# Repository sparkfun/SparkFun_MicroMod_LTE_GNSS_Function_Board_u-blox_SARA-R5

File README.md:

SparkFun MicroMod LTE GNSS Function Board - u-blox SARA-R5
========================================

[*SparkFun MicroMod LTE GNSS Function Board - u-blox SARA-R5 (DEV-18431)*](https://www.sparkfun.com/products/18431)

Using the u-blox SARA-R510M8S, this function board adds LTE and GNSS capabilities to the MicroMod EcoSystem.

Documentation
--------------
* **[Library](https://github.com/sparkfun/SparkFun_u-blox_SARA-R5_Arduino_Library)** - Arduino library for the SparkFun MicroMod LTE GNSS Function Board u-blox SARA-R5.
* **[Hookup Guide](https://docs.sparkfun.com/SparkFun_MicroMod_LTE_GNSS_Function_Board_u-blox_SARA-R5)** - Basic hookup guide for the SparkFun MicroMod LTE GNSS Function Board u-blox SARA-R5.

Product Versions
----------------
* [DEV-18431](https://www.sparkfun.com/products/18431) - Initial release, v1.1

License Information
-------------------

This product is _**open source**_!

Please review the LICENSE.md file for license information.

If you have any questions or concerns on licensing, please contact technical support on our [SparkFun forums](https://forum.sparkfun.com/viewforum.php?f=152).

Distributed as-is; no warranty is given.

- Your friends at SparkFun.

_<COLLABORATION CREDIT>_

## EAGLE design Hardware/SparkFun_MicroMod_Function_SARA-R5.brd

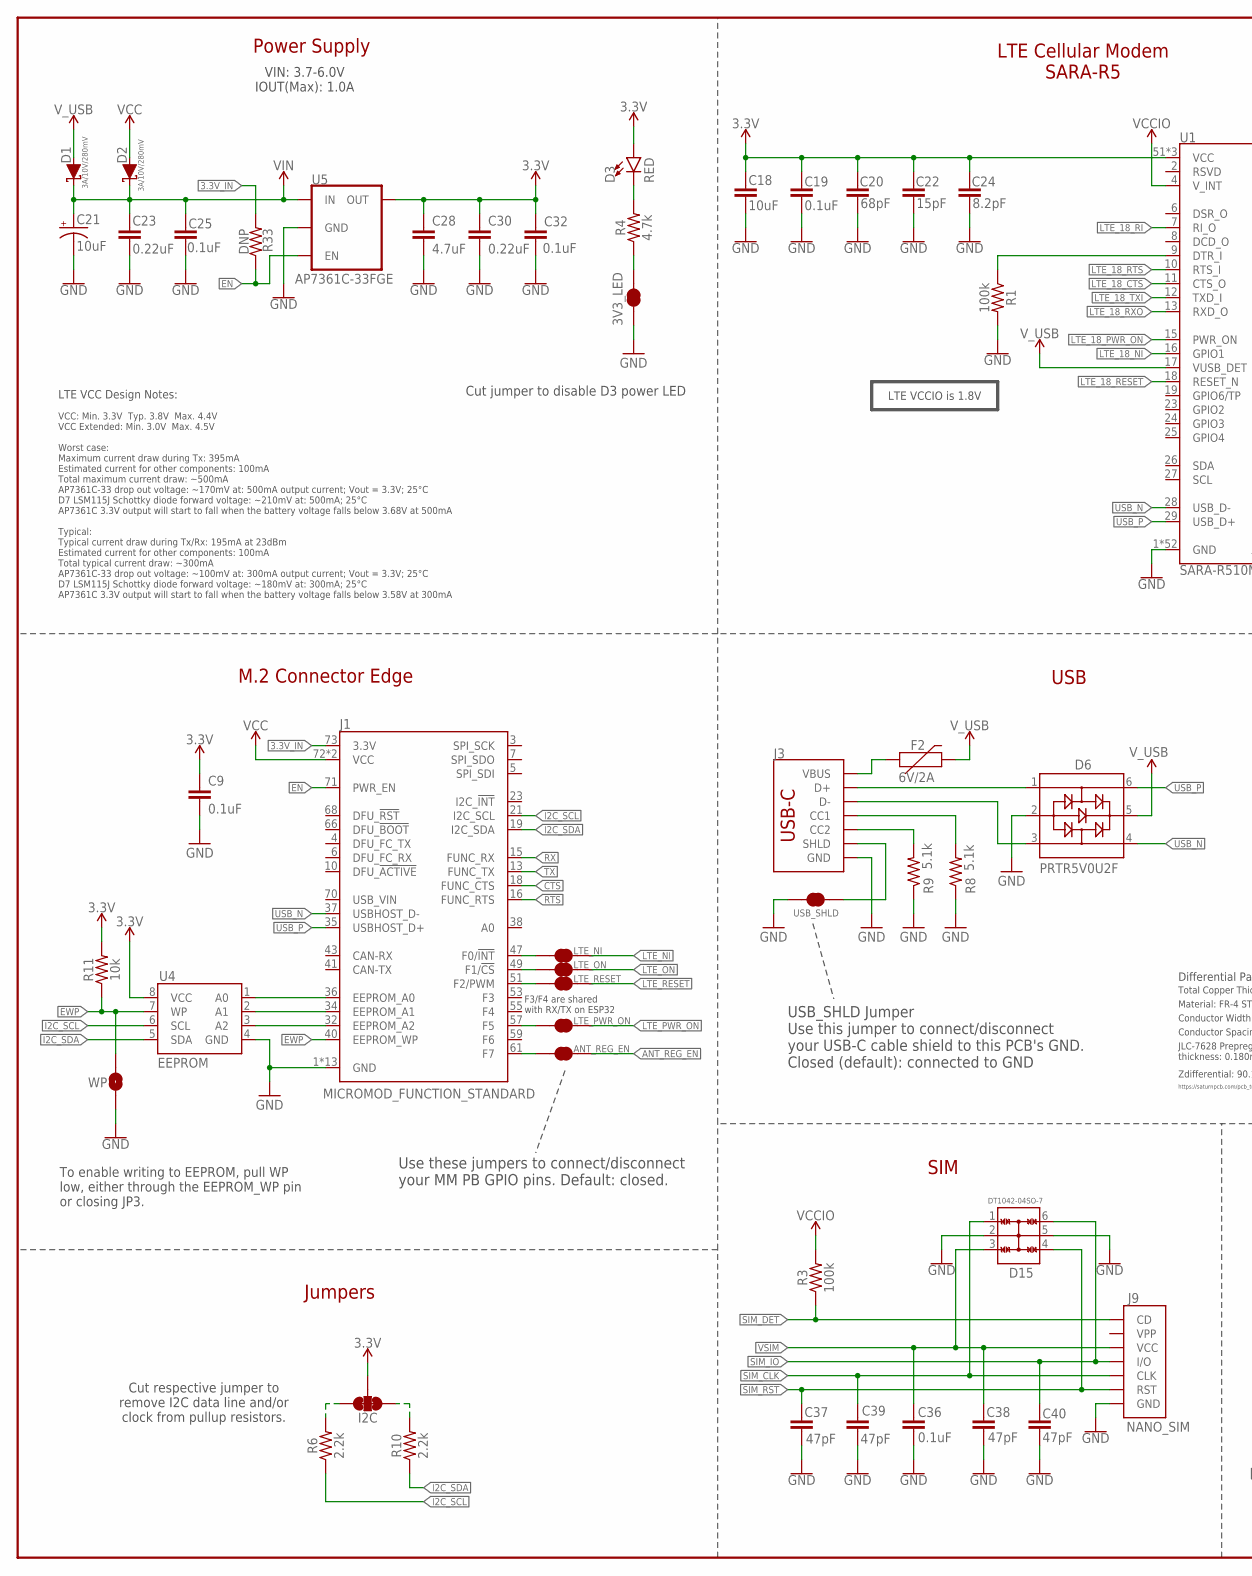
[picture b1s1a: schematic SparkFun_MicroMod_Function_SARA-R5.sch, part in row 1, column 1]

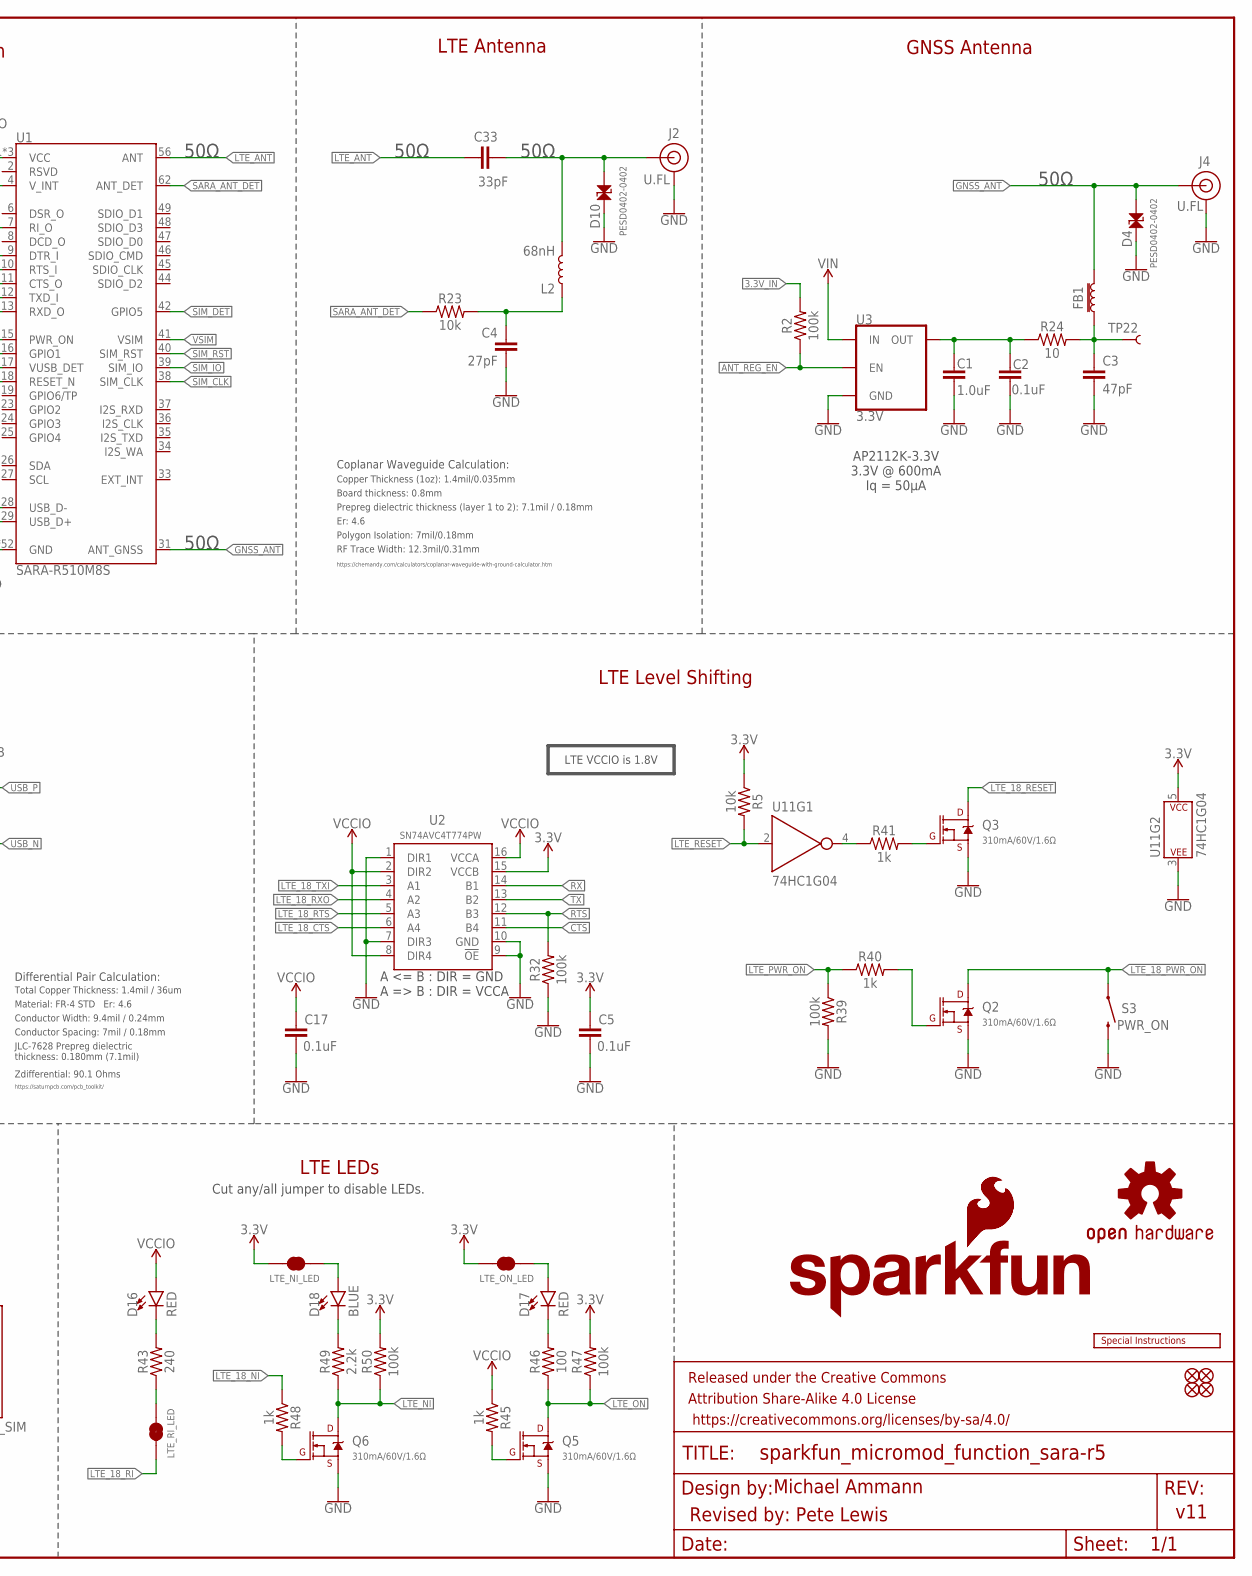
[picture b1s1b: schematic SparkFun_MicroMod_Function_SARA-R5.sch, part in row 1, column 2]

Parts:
3V3_LED: JUMPER-SMT_2_NC_TRACE_SILK; SMT-JUMPER_2_NC_TRACE_SILK
ANT_REG_EN: JUMPER-SMT_2_NC_TRACE_SILK; SMT-JUMPER_2_NC_TRACE_SILK
C1: 1.0uF; 0603
C2, C5, C9, C17, C19, C25, C32, C36: 0.1uF; 0402-TIGHT
C3, C37, C38, C39, C40: 47pF; 0603
C4: 27pF; 0402
C18: 10uF; 0603
C20: 68pF; 0603
C21: 10uF; EIA3216
C22: 15pF; 0603
C23, C30: 0.22uF; 0603
C24: 8.2pF; 0603
C28: 4.7uF; 0603
C33: 33pF; 0402-TIGHT
D1, D2: 3A/10V/280mV; SOD-323
D3, D16, D17: RED; LED-0603
D4, D10: PESD0402-0402; 0402
D6: PRTR5V0U2F; SOT886
D15: DT1042-04SO-7; SOT23-6L
D18: BLUE; LED-0603
F2: 6V/2A; 1210
FB1: 30Ω/1.8A; 0603
FD1, FD2, FD3, FD4: FIDUCIALUFIDUCIAL; FIDUCIAL-MICRO
FRAME2: FRAME-LEDGER; CREATIVE_COMMONS
I2C: JUMPER-SMT_3_2-NC_TRACE_SILK; SMT-JUMPER_3_2-NC_TRACE_SILK
J1: MICROMOD_FUNCTION_STANDARD; M.2-CARD-E-22_FUNCTION_STANDARD
J2, J4: U.FL
J3: USB_C_2-LAYER_PADS; USB-C-16P-2LAYER-PADS
J9: NANO_SIM; NANO_SIM_PP
L2: 68nH; 0402_COILCRAFT
LOGO1: SFE_LOGO_NAME_FLAME.2_INCH; SFE_LOGO_NAME_FLAME_.2
LOGO2: SFE_LOGO_FLAME.2_INCH; SFE_LOGO_FLAME_.2
LOGO3: SPECIAL_INSTRUCTIONS-ORDERING; ORDERING_INSTRUCTIONS
LOGO4: OSHW-LOGOMINI; OSHW-LOGO-MINI
LTE_NI: JUMPER-SMT_2_NC_TRACE_SILK; SMT-JUMPER_2_NC_TRACE_SILK
LTE_NI_LED: JUMPER-SMT_2_NC_TRACE_SILK; SMT-JUMPER_2_NC_TRACE_SILK
LTE_ON: JUMPER-SMT_2_NC_TRACE_SILK; SMT-JUMPER_2_NC_TRACE_SILK
LTE_ON_LED: JUMPER-SMT_2_NC_TRACE_SILK; SMT-JUMPER_2_NC_TRACE_SILK
LTE_PWR_ON: JUMPER-SMT_2_NC_TRACE_SILK; SMT-JUMPER_2_NC_TRACE_SILK
LTE_RESET: JUMPER-SMT_2_NC_TRACE_SILK; SMT-JUMPER_2_NC_TRACE_SILK
LTE_RI_LED: JUMPER-SMT_2_NC_TRACE_SILK; SMT-JUMPER_2_NC_TRACE_SILK
Q2, Q3, Q5, Q6: 310mA/60V/1.6Ω; SOT323
R1, R2, R3, R32, R39, R47, R50: 100k; 0402-TIGHT
R4: 4.7k; 0402-TIGHT
R5, R11, R23: 10k; 0402-TIGHT
R6, R10, R49: 2.2k; 0402-TIGHT
R8, R9: 5.1k; 0402-TIGHT
R24: 10; 0603
R33: DNP; 0402-TIGHT
R40, R41, R45, R48: 1k; 0402-TIGHT
R43: 240; 0603
R46: 100; 0603
S3: PWR_ON; TACTILE_SWITCH_SMD_4.6X2.8MM
TP22: TEST-POINT3X4; PAD.03X.04
U1: SARA-R510M8S; SARA-LGA
U2: SN74AVC4T774PW; SOP65P640X120-16N
U3: 3.3V; SOT23-5
U4: EEPROM; SO08
U5: AP7361C-33FGE; UDFN-8
U11: 74HC1G04; SOT353
USB_SHLD: JUMPER-SMT_2_NC_TRACE_SILK; SMT-JUMPER_2_NC_TRACE_SILK
WP: JUMPER-SMT_2_NO_SILK; SMT-JUMPER_2_NO_SILK

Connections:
3.3V: C5.1, C9.1, C18.1, C19.1, C20.1, C22.1, C24.1, C28.1, C30.1, C32.1, D3.A, I2C.2, LTE_NI_LED.2, LTE_ON_LED.2, R5.1, R11.2, R47.2, R50.2, U1.51 (VCC), U1.52 (VCC), U1.53 (VCC), U2.15 (VCCB), U4.8 (VCC), U5.1 (OUT), U11.5 (P$V+)
3.3V_IN: J1.73 (3.3V), R2.2, R33.2
ANT_REG_EN: ANT_REG_EN.1, R2.1, U3.3 (EN)
CTS: J1.18 (FUNC_CTS), U2.11 (B4)
EN: J1.71 (PWR_EN), R33.1, U5.5 (EN)
EWP: J1.40 (EEPROM_WP), R11.1, U4.7 (WP), WP.2
GND: 3V3_LED.1, C1.2, C2.2, C3.2, C4.2, C5.2, C9.2, C17.2, C18.2, C19.2, C20.2, C21.-, C22.2, C23.2, C24.2, C25.2, C28.2, C30.2, C32.2, C36.1, C37.2, C38.1, C39.2, C40.1, D4.2, D6.2, D10.2, D15.2, D15.5, J1.1 (GND), J1.2 (GND), J1.8 (GND), J1.33 (GND), J1.39 (GND), J1.45 (GND), J1.75 (GND), J1.GND1 (GND), J1.GND2 (GND), J1.GND3 (GND), J1.GND4 (GND), J1.GND5 (GND), J1.GND6 (GND), J2.1 (GND), J2.2 (GND), J3.GND, J3.GND2 (GND), J4.1 (GND), J4.2 (GND), J9.A1 (GND), J9.A2 (GND), J9.A3 (GND), J9.A4 (GND), J9.C5 (GND), Q2.2 (S), Q3.2 (S), Q5.2 (S), Q6.2 (S), R1.2, R8.1, R9.1, R32.1, R39.2, S3.3 (2), S3.4 (2), U1.1 (GND), U1.3 (GND), U1.5 (GND), U1.14 (GND), U1.20 (GND), U1.21 (GND), U1.22 (GND), U1.30 (GND), U1.32 (GND), U1.43 (GND), U1.50 (GND), U1.54 (GND), U1.55 (GND), U1.57 (GND), U1.58 (GND), U1.59 (GND), U1.60 (GND), U1.61 (GND), U1.63 (GND), U1.64 (GND), U1.65 (GND), U1.66 (GND), U1.67 (GND), U1.68 (GND), U1.69 (GND), U1.70 (GND), U1.71 (GND), U1.72 (GND), U1.73 (GND), U1.74 (GND), U1.75 (GND), U1.76 (GND), U1.77 (GND), U1.78 (GND), U1.79 (GND), U1.80 (GND), U1.81 (GND), U1.82 (GND), U1.83 (GND), U1.84 (GND), U1.85 (GND), U1.86 (GND), U1.87 (GND), U1.88 (GND), U1.89 (GND), U1.90 (GND), U1.91 (GND), U1.92 (GND), U1.93 (GND), U1.94 (GND), U1.95 (GND), U1.96 (GND), U2.1 (DIR1), U2.7 (DIR3), U2.9 (!OE), U2.10 (GND), U3.2 (GND), U4.4 (GND), U5.4 (GND), U5.EP (GND), U11.3 (P$V-), USB_SHLD.2, WP.1
GNSS_ANT: D4.1, FB1.2, J4.FEED (SIGNAL), U1.31 (ANT_GNSS)
I2C_SCL: J1.21 (I2C_SCL), R6.1, U4.6 (SCL)
I2C_SDA: J1.19 (I2C_SDA), R10.1, U4.5 (SDA)
LTE_18_!RESET!: Q3.3 (D), U1.18 (RESET_N)
LTE_18_CTS: U1.11 (CTS_O), U2.6 (A4)
LTE_18_DTR: R1.1, U1.9 (DTR_I)
LTE_18_NI: R48.1, U1.16 (GPIO1)
LTE_18_PWR_ON: Q2.3 (D), S3.1, S3.2 (1), U1.15 (PWR_ON)
LTE_18_RI: LTE_RI_LED.2, U1.7 (RI_O)
LTE_18_RTS: U1.10 (RTS_I), U2.5 (A3)
LTE_18_RXO: U1.13 (RXD_O), U2.4 (A2)
LTE_18_TXI: U1.12 (TXD_I), U2.3 (A1)
LTE_!NI!: LTE_NI.1, Q6.3 (D), R49.1, R50.1
LTE_!ON!: LTE_ON.1, Q5.3 (D), R46.1, R47.1
LTE_!RESET!: LTE_RESET.1, R5.2, U11.2 (A)
LTE_ANT: C33.1, U1.56 (ANT)
LTE_PWR_ON: LTE_PWR_ON.1, R39.1, R40.1
unnamed: J1.36 (EEPROM_A0), U4.1 (A0)
unnamed: J3.A5 (CC1), R8.2
unnamed: J1.57 (F5), LTE_PWR_ON.2
unnamed: ANT_REG_EN.2, J1.61 (F7)
unnamed: J3.B5 (CC2), R9.2
unnamed: 3V3_LED.2, R4.1
unnamed: D3.C, R4.2
unnamed: J1.32 (EEPROM_A2), U4.3 (A2)
unnamed: J1.34 (EEPROM_A1), U4.2 (A1)
unnamed: D6.1, J3.A6 (D+), J3.B6 (D+)
unnamed: C33.2, D10.1, J2.FEED (SIGNAL), L2.P$2 (2)
unnamed: J1.47 (F0/!INT!), LTE_NI.2
unnamed: I2C.1, R10.2
unnamed: I2C.3, R6.2
unnamed: D6.3, J3.A7 (D-), J3.B7 (D-)
unnamed: J1.49 (F1/!CS!), LTE_ON.2
unnamed: J1.51 (F2/PWM), LTE_RESET.2
unnamed: C4.1, L2.P$1 (1), R23.2
unnamed: D18.A, LTE_NI_LED.1
unnamed: LTE_RI_LED.1, R43.1
unnamed: D17.A, LTE_ON_LED.1
unnamed: F2.1, J3.VBUS1 (VBUS), J3.VBUS2 (VBUS)
unnamed: C1.1, C2.1, R24.1, U3.5 (OUT)
unnamed: C3.1, FB1.1, R24.2, TP22.1
unnamed: Q2.1 (G), R40.2
unnamed: Q3.1 (G), R41.2
unnamed: R41.1, U11.4 (Y)
unnamed: D16.C, R43.2
unnamed: Q6.1 (G), R48.2
unnamed: D18.C, R49.2
unnamed: Q5.1 (G), R45.2
unnamed: D17.C, R46.2
RTS: J1.16 (FUNC_RTS), R32.2, U2.12 (B3)
RX: J1.15 (FUNC_RX), U2.14 (B1)
SARA_ANT_DET: R23.1, U1.62 (ANT_DET)
SHLD: J3.SHLD1 (SHLD), J3.SHLD2 (SHLD), J3.SHLD3 (SHLD), J3.SHLD4 (SHLD), USB_SHLD.1
SIM_CLK: C39.1, D15.1, J9.C3 (CLK), U1.38 (SIM_CLK)
SIM_DET: J9.CD, R3.1, U1.42 (GPIO5)
SIM_IO: C40.2, D15.6, J9.C7 (I/O), U1.39 (SIM_IO)
SIM_RST: C37.1, D15.4, J9.C2 (RST), U1.40 (SIM_RST)
TX: J1.13 (FUNC_TX), U2.13 (B2)
USB_N: D6.4, J1.37 (USBHOST_D-), U1.28 (USB_D-)
USB_P: D6.6, J1.35 (USBHOST_D+), U1.29 (USB_D+)
VCC: D2.A, J1.72 (VCC), J1.74 (VCC)
VCCIO: C17.1, D16.A, R3.2, R45.1, U1.4 (V_INT), U2.2 (DIR2), U2.8 (DIR4), U2.16 (VCCA)
VIN: C21.+, C23.1, C25.1, D1.C, D2.C, U3.1 (IN), U5.8 (IN)
VSIM: C36.2, C38.2, D15.3, J9.C1 (VCC), U1.41 (VSIM)
V_USB: D1.A, D6.5, F2.2, U1.17 (VUSB_DET)

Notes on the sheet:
Michael Ammann
v11
M.2 Connector Edge
Power Supply
Jumpers
Cut respective jumper to remove I2C data line and/or clock from pullup resistors.
To enable writing to EEPROM, pull WP low, either through the EEPROM_WP pin or closing JP3.
Cut jumper to disable D3 power LED
LTE VCC Design Notes:
VCC: Min. 3.3V Typ. 3.8V Max. 4.4V VCC Extended: Min. 3.0V Max. 4.5V Worst case: Maximum current draw during Tx: 395mA Estimated current for other components: 100mA Total maximum current draw: ~500mA AP7361C-33 drop out voltage: ~170mV at: 500mA output current; Vout = 3.3V; 25°C D7 LSM115J Schottky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
VIN: 3.7-6.0V IOUT(Max): 1.0A
LTE Cellular Modem SARA-R5
SIM
50Ω
LTE VCCIO is 1.8V
LTE Antenna
LTE LEDs
LTE Level Shifting
USB
F3/F4 are shared with RX/TX on ESP32
Revised by: Pete Lewis
GNSS Antenna
AP2112K-3.3V 3.3V @ 600mA Iq = 50µA
Material: FR-4 STD Er: 4.6
Total Copper Thickness: 1.4mil / 36um
Conductor Spacing: 7mil / 0.18mm
Conductor Width: 9.4mil / 0.24mm
JLC-7628 Prepreg dielectric thickness: 0.180mm (7.1mil)
https://saturnpcb.com/pcb_toolkit/
Differential Pair Calculation:
Zdifferential: 90.1 Ohms
USB_SHLD Jumper Use this jumper to connect/disconnect your USB-C cable shield to this PCB's GND. Closed (default): connected to GND
Board thickness: 0.8mm
Er: 4.6
Copper Thickness (1oz): 1.4mil/0.035mm
RF Trace Width: 12.3mil/0.31mm
Polygon Isolation: 7mil/0.18mm
Prepreg dielectric thickness (layer 1 to 2): 7.1mil / 0.18mm
https://chemandy.com/calculators/coplanar-waveguide-with-ground-calculator.htm
Coplanar Waveguide Calculation:

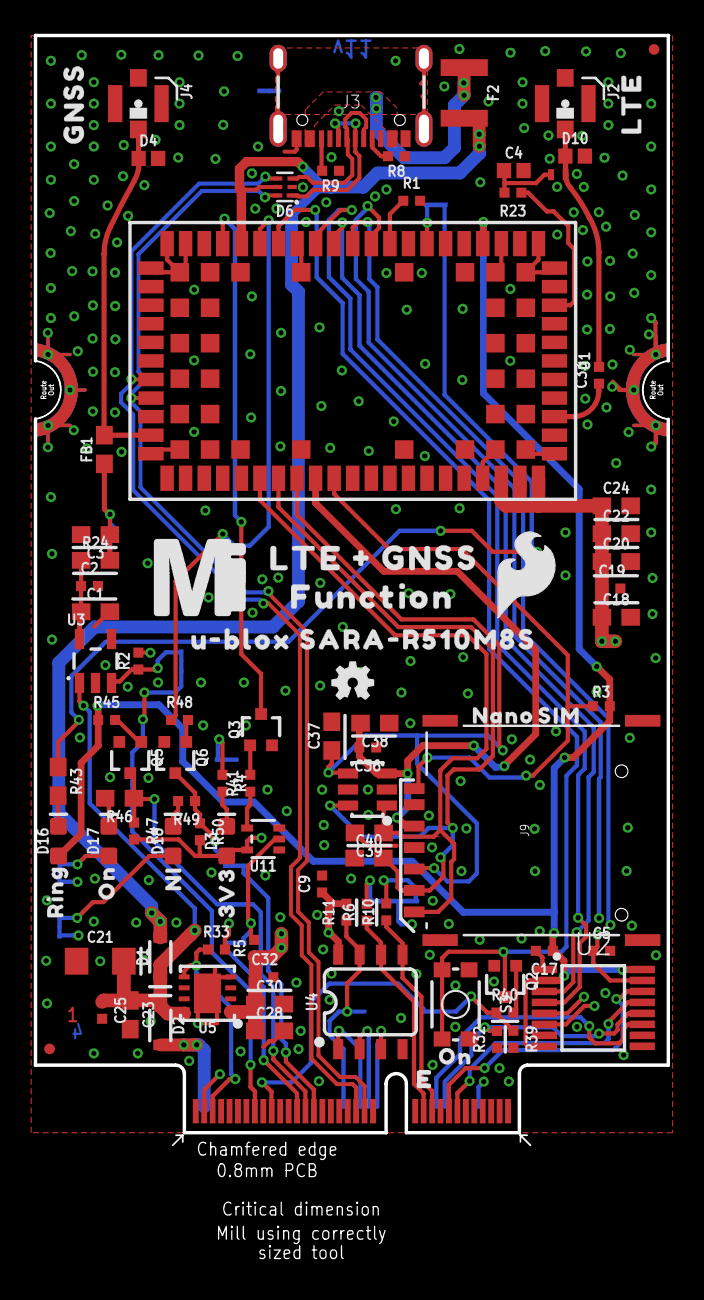
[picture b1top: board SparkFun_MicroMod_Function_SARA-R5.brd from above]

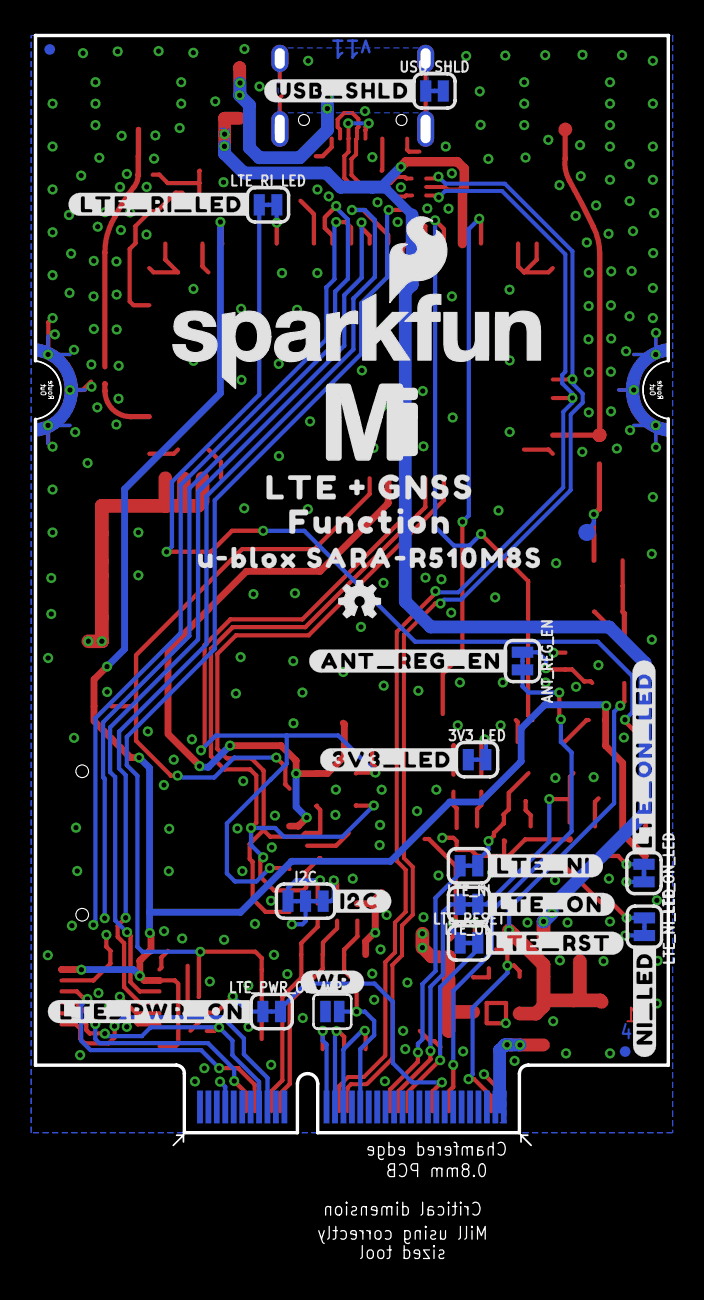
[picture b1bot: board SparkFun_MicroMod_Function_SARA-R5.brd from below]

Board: 4 copper layers, 37.5 x 65.8 mm, 129 parts (33 on the bottom side), 72 nets.

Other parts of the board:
LOGO6: OSHW-LOGOMINI; OSHW-LOGO-MINI
U$1: #I2C#0
U$2: #ANT_REG_EN#0
U$3, U$12: MICROMOD_MI_LOGO_1
U$4: #3V3_LED#0
U$5, U$31: ON0
U$6: #LTE_ON#2
U$7: #LTE_NI#2
U$8: #LTE_PWR_ON#1
U$9: #NI_LED#0
U$10: #WP#0
U$11, U$14: LTE_#_GNSS0
U$13, U$19: FUNCTION0
U$15, U$20: U#BLOX_SARA#R510M8S0
U$16: LTE0
U$17: GNSS0
U$18: NANO0
U$21: #USB_SHLD#0
U$22: #LTE_RI_LED#0
U$23: #LTE_RST#0
U$24: #LTE_ON_LED#0
U$29: NI0
U$57: 3V34
U$80: RING0
U$126: SIM0

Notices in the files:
parts and their libraries:
SparkFun-Aesthetics: Licensing: Creative Commons ShareAlike 4.0 International - https://creativecommons.org/licenses/by-sa/4.0
SparkFun-Aesthetics: Released under the Creative Commons Attribution Share-Alike 4.0 License
SparkFun-Aesthetics: https://creativecommons.org/licenses/by-sa/4.0
